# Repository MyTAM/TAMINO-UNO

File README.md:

# TAMINO-UNO
Docs and Drivers for the TAMINO UNO board
-------------------

[  
*TAMINO UNO (TAMINO01)*](http://www.tuttoamenoshop.it/epages/84141.sf/it_IT/?ObjectPath=/Shops/84141/Products/TAMINO01)

TAMINO UNO is an Arduino(TM) like development board fully compatible, designed in Italy.

License Information
-------------------

The hardware design and firmware are released under [Creative Commons Share-alike 3.0](http://creativecommons.org/licenses/by-sa/3.0/).

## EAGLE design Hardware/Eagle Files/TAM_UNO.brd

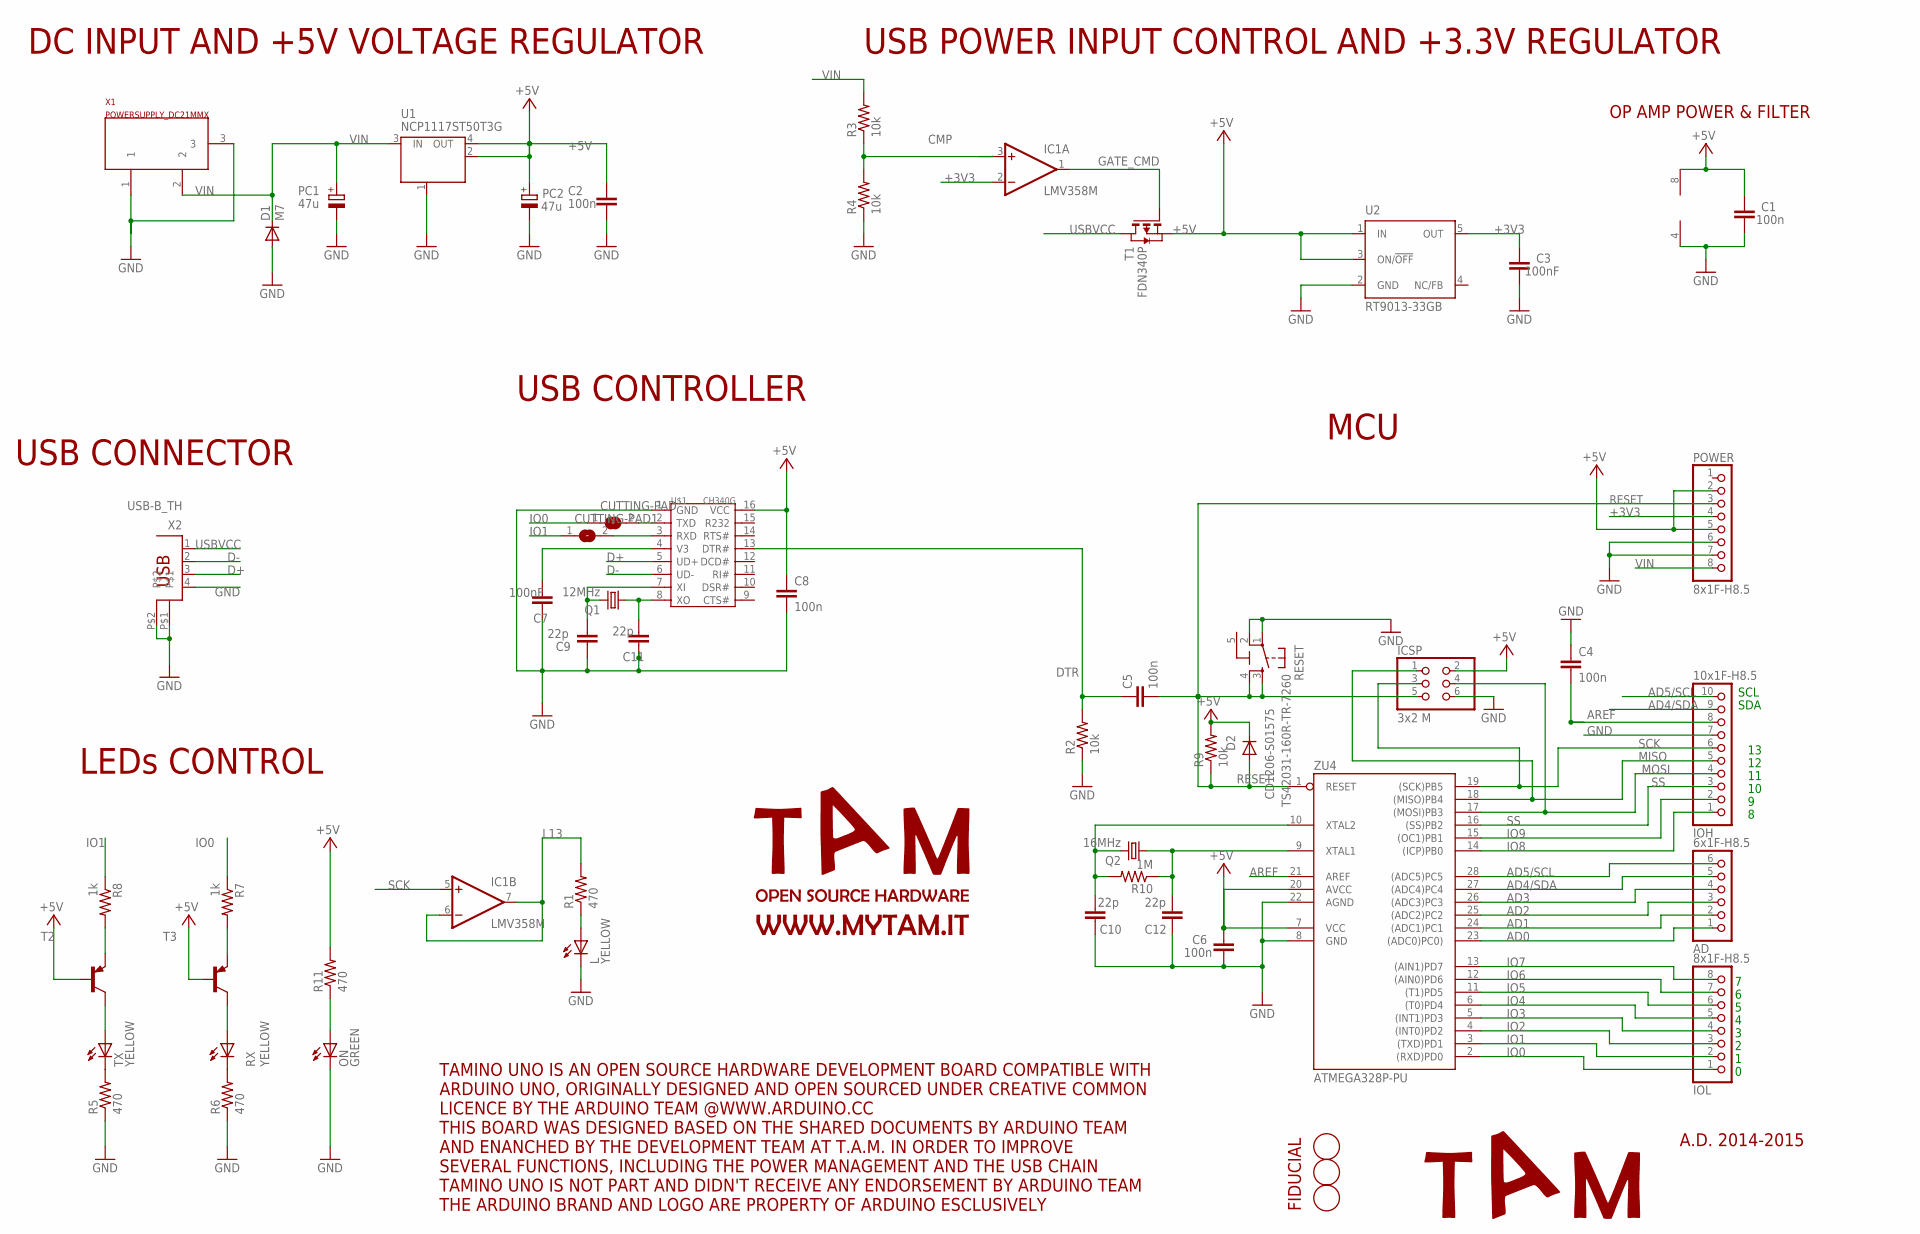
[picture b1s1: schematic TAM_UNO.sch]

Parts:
AD: 6x1F-H8.5; 1X06
C1, C2, C4, C5, C6, C8: 100n; C0603K
C3, C7: 100nF; C0603K
C9, C10, C11, C12: 22p; C0603K
CUTTING-PAD, CUTTING-PAD1: SJ
D1: M7; SMB
D2: CD1206-S01575; MINIMELF
FD1, FD2, FD3: FIDUCIALMOUNT; FIDUCIA-MOUNT
IC1: LMV358M; SO08
ICSP: 3x2 M; 2X03
IOH: 10x1F-H8.5; 1X10
IOL: 8x1F-H8.5; 1X08
L: YELLOW; CHIP-LED0805
ON: GREEN; CHIP-LED0805
PC1, PC2: 47u; PANASONIC_D
POWER: 8x1F-H8.5; 1X08
Q1: 12MHz; SM49
Q2: 16MHz; SM49
R1, R5, R6, R11: 470; R0603
R2, R3, R4, R9: 10k; R0603
R7, R8: 1k; R0603
R10: 1M; R0603
RESET: TS42031-160R-TR-7260; TS42
RX: YELLOW; CHIP-LED0805
T1: FDN340P; SOT-23
T2, T3: -PNP-SOT23-EBC; SOT23-EBC
TX: YELLOW; CHIP-LED0805
U1: NCP1117ST50T3G; SOT223
U2: RT9013-33GB; SOT23-DBV
U$1: CH340G; SSOP16
X1: POWERSUPPLY_DC21MMX; POWERSUPPLY_DC-21MM
X2: USB-B_TH; PN61729
ZU4: ATMEGA328P-PU; DIL28-3

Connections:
5-GND: RESET.5 (5-GND)
+3V3: C3.2, IC1.2 (-IN), POWER.4, U2.5 (OUT)
+5V: C1.2, C2.2, C6.2, C8.1, D2.C, IC1.8 (V+), ICSP.2, PC2.+, POWER.2, POWER.5, R9.2, R11.2, T1.2 (S), T2.B, T3.B, U1.2 (OUT), U1.4 (OUT), U2.1 (IN), U2.3 (ON/!OFF), U$1.16 (VCC), ZU4.7 (VCC), ZU4.20 (AVCC)
AD0: AD.1, ZU4.23 ((ADC0)PC0))
AD1: AD.2, ZU4.24 ((ADC1)PC1)
AD2: AD.3, ZU4.25 ((ADC2)PC2)
AD3: AD.4, ZU4.26 ((ADC3)PC3)
AD4/SDA: AD.5, IOH.9, ZU4.27 ((ADC4)PC4)
AD5/SCL: AD.6, IOH.10, ZU4.28 ((ADC5)PC5)
AREF: C4.2, IOH.8, ZU4.21 (AREF)
CMP: IC1.3 (+IN), R3.1, R4.2
D+: U$1.5 (UD+), X2.3
D-: U$1.6 (UD-), X2.2
DTR: C5.1, R2.2, U$1.13 (DTR#)
GATE_CMD: IC1.1 (OUT), T1.3 (G)
GND: C1.1, C2.1, C3.1, C4.1, C6.1, C7.2, C8.2, C9.2, C10.2, C11.2, C12.2, D1.A, IC1.4 (V-), ICSP.6, IOH.7, L.C, ON.C, PC1.-, PC2.-, POWER.6, POWER.7, R2.1, R4.1, R5.1, R6.1, RESET.1, RESET.2, U1.1 (GND/ADJ), U2.2 (GND), U$1.1 (GND), X1.1, X1.3, X2.4, X2.P$1, X2.P$2, ZU4.8 (GND), ZU4.22 (AGND)
IO0: CUTTING-PAD.1, IOL.1, R7.1, ZU4.2 ((RXD)PD0)
IO1: CUTTING-PAD1.1, IOL.2, R8.1, ZU4.3 ((TXD)PD1)
IO2: IOL.3, ZU4.4 ((INT0)PD2)
IO3: IOL.4, ZU4.5 ((INT1)PD3)
IO4: IOL.5, ZU4.6 ((T0)PD4)
IO5: IOL.6, ZU4.11 ((T1)PD5)
IO6: IOL.7, ZU4.12 ((AIN0)PD6)
IO7: IOL.8, ZU4.13 ((AIN1)PD7)
IO8: IOH.1, ZU4.14 ((ICP)PB0)
IO9: IOH.2, ZU4.15 ((OC1)PB1)
L13: IC1.6 (-IN), IC1.7 (OUT), R1.2
MISO: ICSP.1, IOH.5, ZU4.18 ((MISO)PB4)
MOSI: ICSP.4, IOH.4, ZU4.17 ((MOSI)PB3)
unnamed: L.A, R1.1
unnamed: C9.1, Q1.2, U$1.7 (XI)
unnamed: ON.A, R11.1
unnamed: C11.1, Q1.1, U$1.8 (XO)
unnamed: R5.2, TX.C
unnamed: R6.2, RX.C
unnamed: R8.2, T2.E
unnamed: R7.2, T3.E
unnamed: T2.C, TX.A
unnamed: RX.A, T3.C
unnamed: C10.1, Q2.2, R10.2, ZU4.10 (XTAL2)
unnamed: C12.1, Q2.1, R10.1, ZU4.9 (XTAL1)
unnamed: CUTTING-PAD.2, U$1.2 (TXD)
unnamed: CUTTING-PAD1.2, U$1.3 (RXD)
RESET: C5.2, D2.A, ICSP.5, POWER.3, R9.1, RESET.3, RESET.4, ZU4.1 (RESET)
SCK: IC1.5 (+IN), ICSP.3, IOH.6, ZU4.19 ((SCK)PB5)
SS: IOH.3, ZU4.16 ((SS)PB2)
USBVCC: T1.1 (D), X2.1
V3: C7.1, U$1.4 (V3)
VIN: D1.C, PC1.+, POWER.8, R3.2, U1.3 (IN), X1.2

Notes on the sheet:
SDA
SCL
DC INPUT AND +5V VOLTAGE REGULATOR
USB POWER INPUT CONTROL AND +3.3V REGULATOR
OP AMP POWER & FILTER
FIDUCIAL
USB CONNECTOR
USB CONTROLLER
MCU
LEDs CONTROL
TAMINO UNO IS AN OPEN SOURCE HARDWARE DEVELOPMENT BOARD COMPATIBLE WITH ARDUINO UNO, ORIGINALLY DESIGNED AND OPEN SOURCED UNDER CREATIVE COMMON LICENCE BY THE ARDUINO TEAM @WWW.ARDUINO.CC THIS BOARD WAS DESIGNED BASED ON THE SHARED DOCUMENTS BY ARDUINO TEAM AND ENANCHED BY THE DEVELOPMENT TEAM AT T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
A.D. 2014-2015

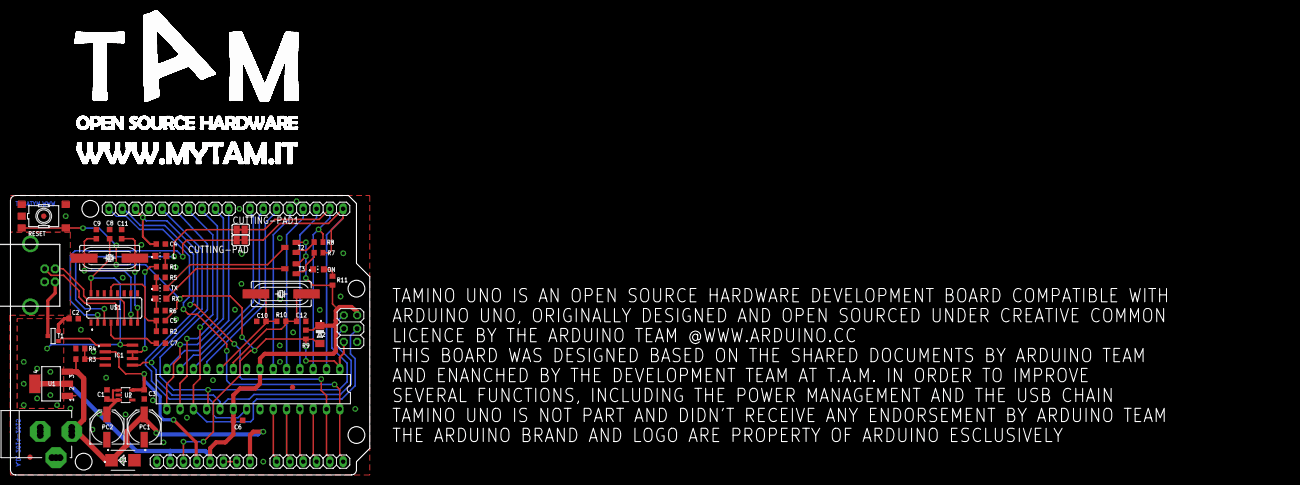
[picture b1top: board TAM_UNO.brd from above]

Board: 2 copper layers, 244.1 x 88.7 mm, 54 parts (0 on the bottom side), 48 nets.

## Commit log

2015-12-03 Published the design files
    Published the design files including PDF schematics, Eagle Schematics
    and Board files, PCB's Gerber files and BOM
